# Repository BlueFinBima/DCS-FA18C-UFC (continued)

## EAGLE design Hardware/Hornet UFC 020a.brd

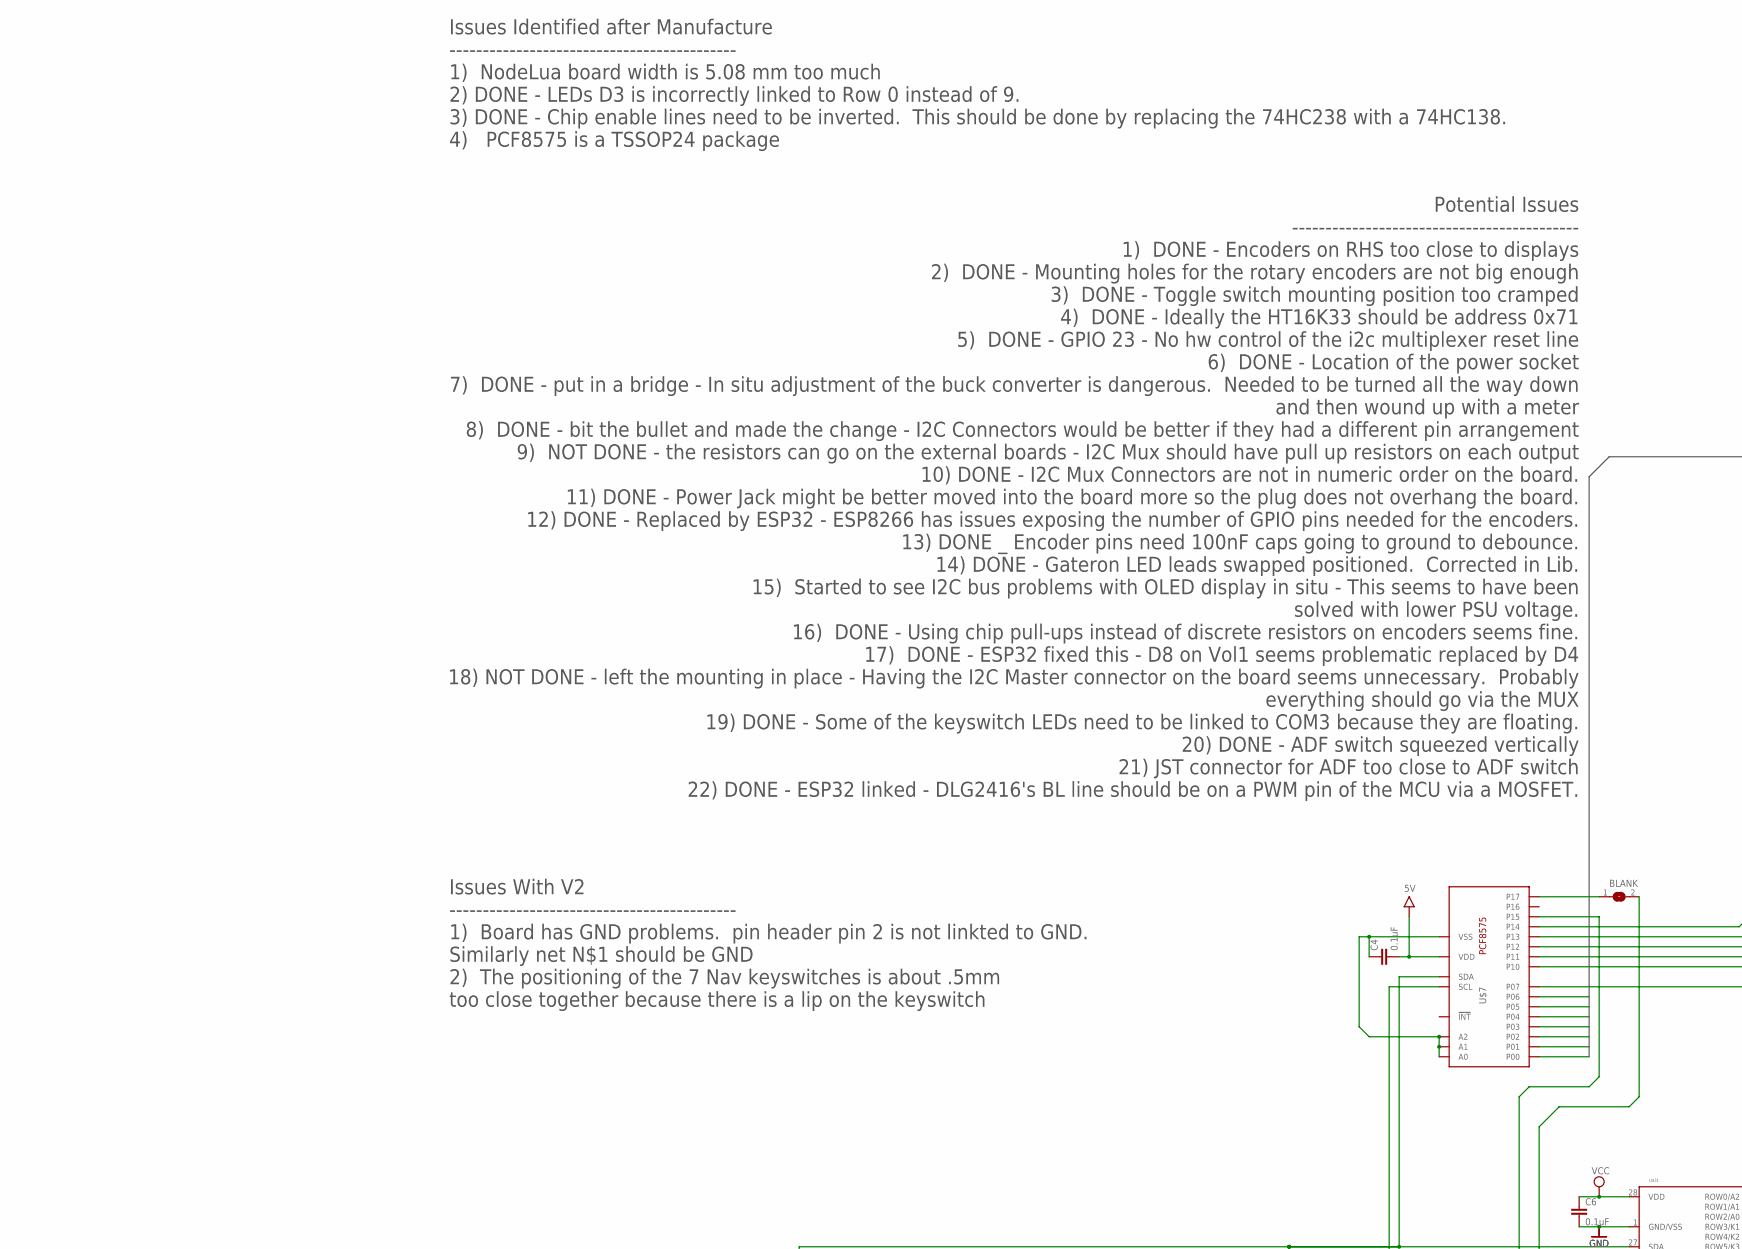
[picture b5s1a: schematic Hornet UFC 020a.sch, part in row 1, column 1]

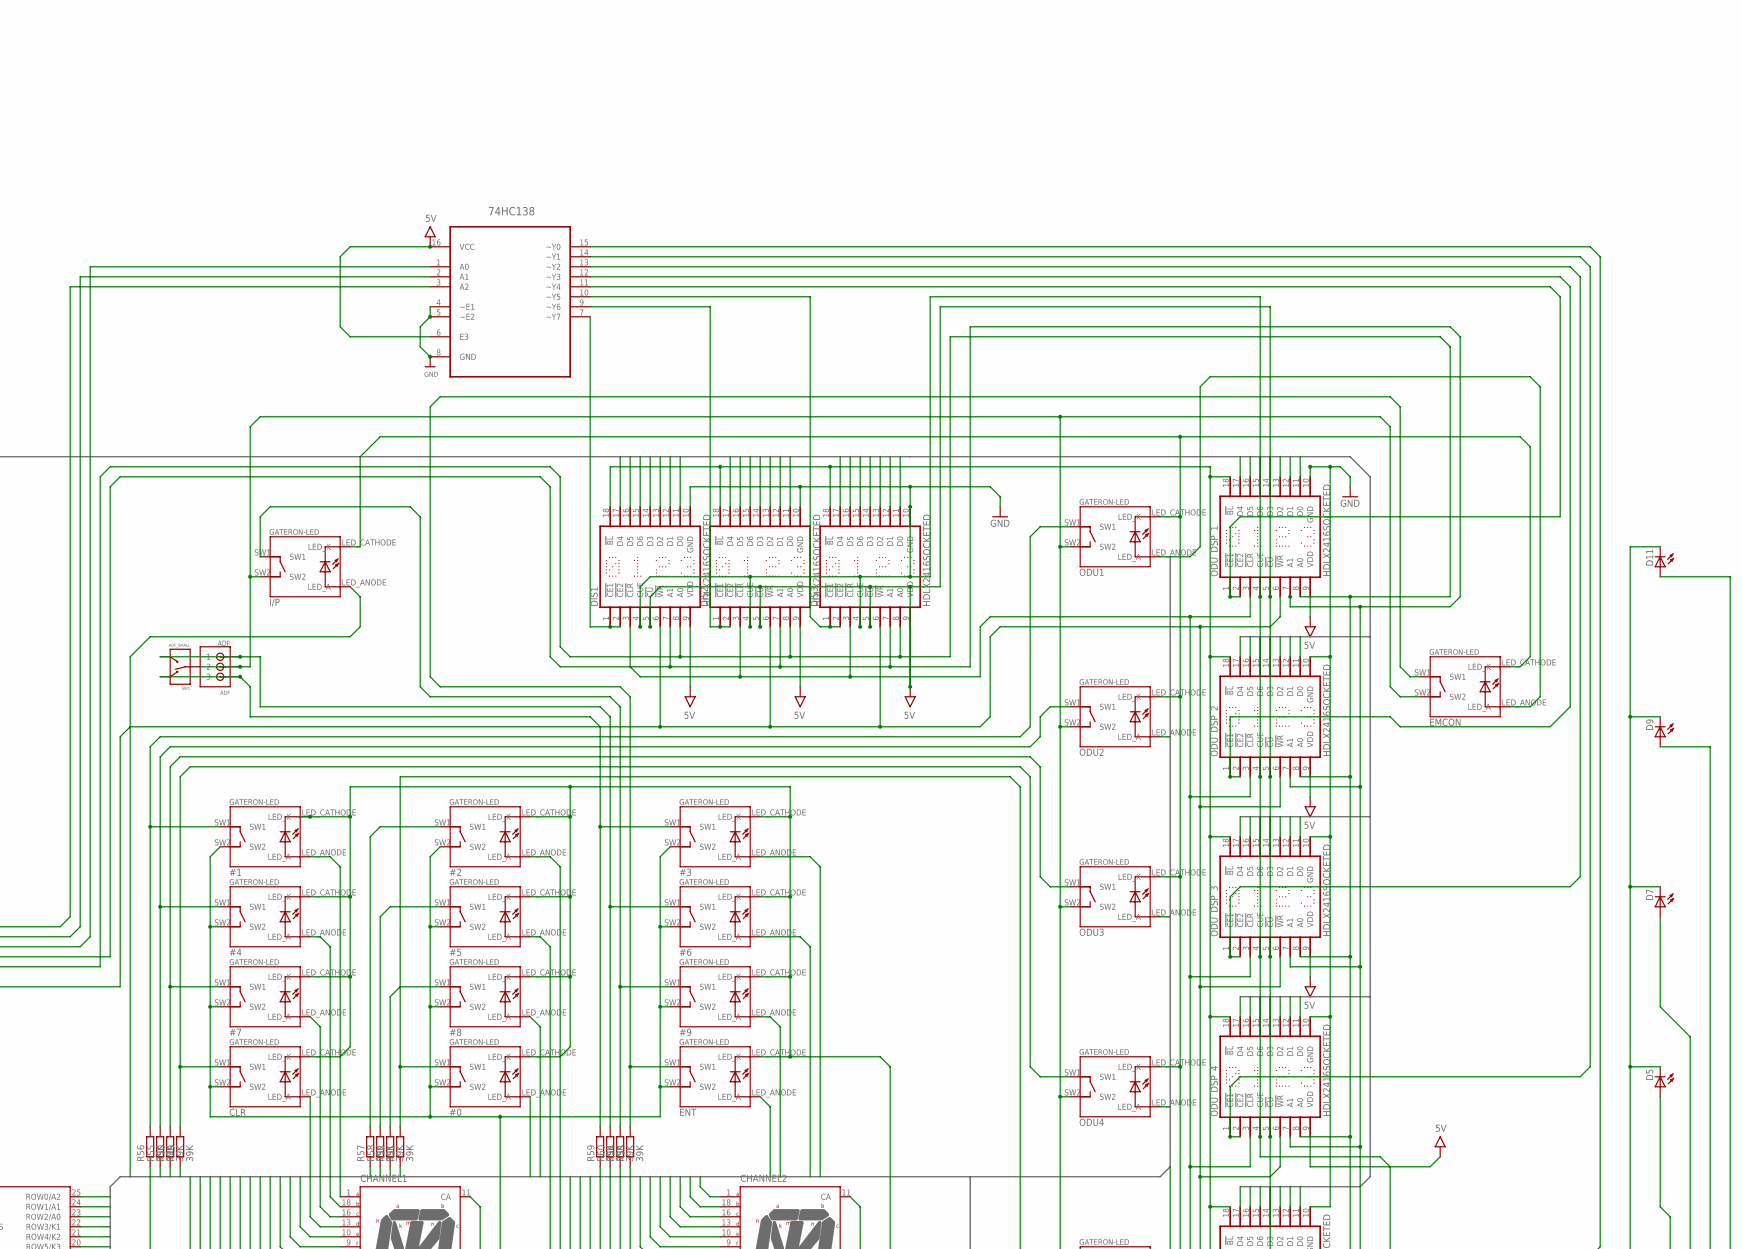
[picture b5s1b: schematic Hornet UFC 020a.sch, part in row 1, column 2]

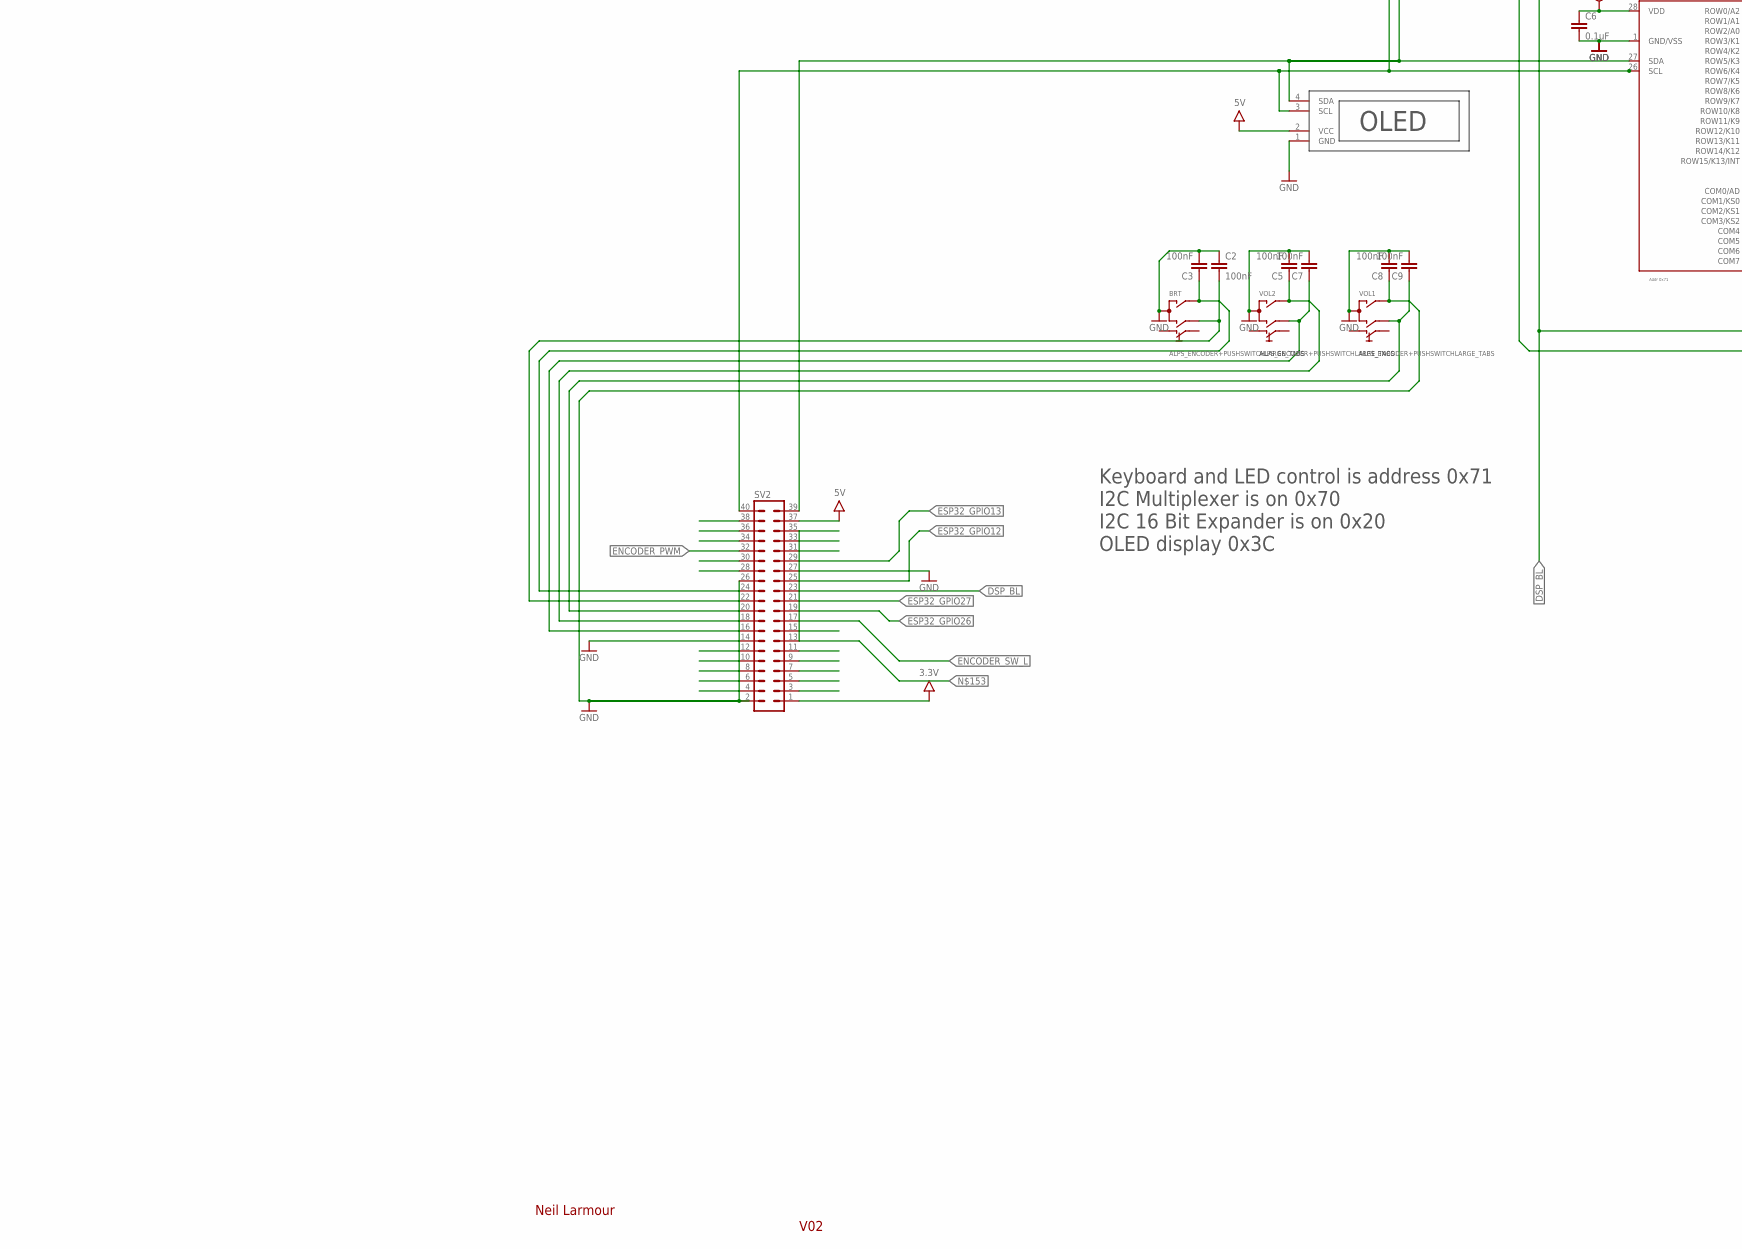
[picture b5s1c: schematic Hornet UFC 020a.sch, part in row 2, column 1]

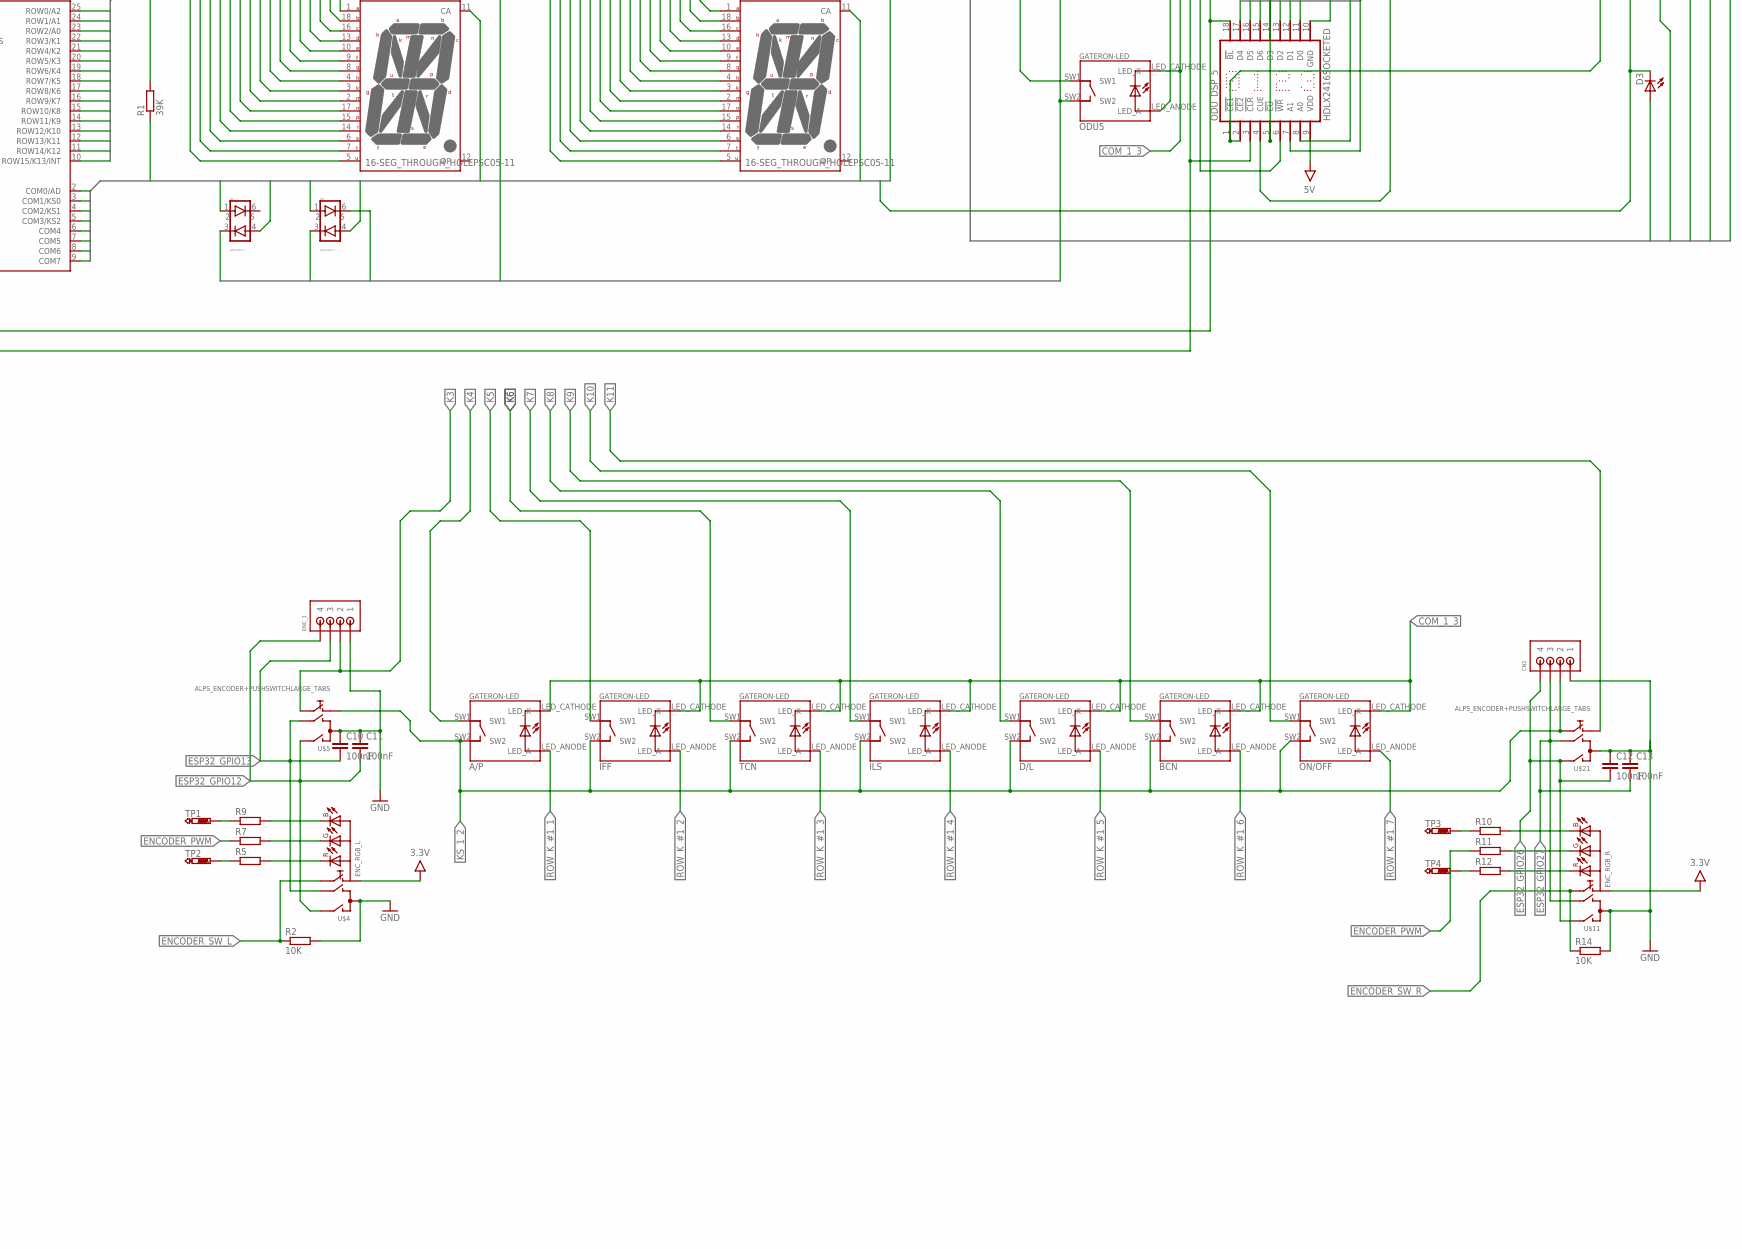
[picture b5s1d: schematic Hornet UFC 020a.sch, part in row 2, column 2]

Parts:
74HC138: CD74HC138M; SOIC127P600X175-16N
#0, #1, #2, #3, #4, #5, #6, #7, #8, #9: GATERON-LED
A/P: GATERON-LED
ADF: ADF; B3B-PH-SOLDER
BCN: GATERON-LED
BLANK: SOLDERJUMPERCLOSED; SOLDERJUMPER_CLOSEDWIRE
BRT: ALPS_ENCODER+PUSHSWITCHLARGE_TABS; ENCODER+SWITCH_LARGER_TABS
C2, C3, C5, C7, C8, C9, C10, C11, C12, C13: 100nF; C0805
C4, C6: 0.1uF; C0805
CHANNEL1, CHANNEL2: 16-SEG_THROUGH_HOLEPSC05-11; PSC05-11
CLR: GATERON-LED
CN2: JST-PH-B4B-PH-SM4THRU-HOLE; B4B-PH-SOLDER
D1, D2: BAT54CDW-7-F; SSOT6
D3, D5, D7, D9, D11: LED3MM_V_OFFSET; LED5X2MM_RECT_3MM_VOFFSET
D/L: GATERON-LED
DIS1, DIS2, DIS3: HDLX2416SOCKETED; HDLX2416(SOCKETED)
EMCON: GATERON-LED
ENC_1: JST-PH-B4B-PH-SM4THRU-HOLE; B4B-PH-SOLDER
ENT: GATERON-LED
I/P: GATERON-LED
IFF: GATERON-LED
ILS: GATERON-LED
ODU1, ODU2, ODU3, ODU4, ODU5: GATERON-LED
ODU_DSP_1, ODU_DSP_2, ODU_DSP_3, ODU_DSP_4, ODU_DSP_5: HDLX2416SOCKETED; HDLX2416(SOCKETED)
ON/OFF: GATERON-LED
R1, R49, R50, R51, R52, R53, R54, R55, R56, R57, R58, R59, R60: 39K; R1206
R2, R14: 10K; R0805
R5, R7, R9, R10, R11, R12: R-EU_R0805; R0805
SV2: MA20-2
SW1: ADF_SMALL; MICRO_TOGGLE_SPDT
TCN: GATERON-LED
TP1, TP2, TP3, TP4: PTR1TP13SQ; TP13SQ
U$4: ENC_RGB_L; ENCODER_RGB
U$5, U$21: ALPS_ENCODER+PUSHSWITCHLARGE_TABS; ENCODER+SWITCH_LARGER_TABS
U$7: PCF8575PWR; TSSOP24
U$11: ENC_RGB_R; ENCODER_RGB
U$31: Addr 0x71; SOIC28
U$37: OLED_128X32_I2C_DISPLAYTHROUGH_HOLE; OLED128X32_GRAPHICS_MODULE
VOL1, VOL2: ALPS_ENCODER+PUSHSWITCHLARGE_TABS; ENCODER+SWITCH_LARGER_TABS

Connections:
3.3V: U$4.ANODE (VCC), U$11.ANODE (VCC)
3V3: SV2.1
5V: 74HC138.6 (E3), 74HC138.16 (VCC), C4.2, C6.1, DIS1.5 (!CU), DIS1.9 (VDD), DIS2.5 (!CU), DIS2.9 (VDD), DIS3.5 (!CU), DIS3.9 (VDD), ODU_DSP_1.5 (!CU), ODU_DSP_1.9 (VDD), ODU_DSP_2.5 (!CU), ODU_DSP_2.9 (VDD), ODU_DSP_3.5 (!CU), ODU_DSP_3.9 (VDD), ODU_DSP_4.5 (!CU), ODU_DSP_4.9 (VDD), ODU_DSP_5.5 (!CU), ODU_DSP_5.9 (VDD), SV2.37, U$7.24 (VDD), U$31.28 (VDD), U$37.2 (VCC)
COM_1_0: CHANNEL1.11 (CA), D1.1 (A1), R1.1, U$31.2 (COM0/AD)
COM_1_1: CHANNEL2.11 (CA), D1.4 (A2), U$31.3 (COM1/KS0)
COM_1_2: #0.LED_CATHODE (LED_K), #1.LED_CATHODE (LED_K), #2.LED_CATHODE (LED_K), #3.LED_CATHODE (LED_K), #4.LED_CATHODE (LED_K), #5.LED_CATHODE (LED_K), #6.LED_CATHODE (LED_K), #7.LED_CATHODE (LED_K), #8.LED_CATHODE (LED_K), #9.LED_CATHODE (LED_K), CLR.LED_CATHODE (LED_K), D2.1 (A1), ENT.LED_CATHODE (LED_K), U$31.4 (COM2/KS1)
COM_1_3: A/P.LED_CATHODE (LED_K), BCN.LED_CATHODE (LED_K), D2.4 (A2), D/L.LED_CATHODE (LED_K), EMCON.LED_CATHODE (LED_K), I/P.LED_CATHODE (LED_K), IFF.LED_CATHODE (LED_K), ILS.LED_CATHODE (LED_K), ODU1.LED_CATHODE (LED_K), ODU2.LED_CATHODE (LED_K), ODU3.LED_CATHODE (LED_K), ODU4.LED_CATHODE (LED_K), ODU5.LED_CATHODE (LED_K), ON/OFF.LED_CATHODE (LED_K), TCN.LED_CATHODE (LED_K), U$31.5 (COM3/KS2)
COM_1_4: D3.K (C), D5.K (C), D7.K (C), D9.K (C), D11.K (C), U$31.6 (COM4)
COM_1_5: U$31.7 (COM5)
COM_1_6: U$31.8 (COM6)
COM_1_7: U$31.9 (COM7)
D0: DIS1.11 (D0), DIS2.11 (D0), DIS3.11 (D0), ODU_DSP_1.11 (D0), ODU_DSP_2.11 (D0), ODU_DSP_3.11 (D0), ODU_DSP_4.11 (D0), ODU_DSP_5.11 (D0), U$7.4 (P00)
D1: DIS1.12 (D1), DIS2.12 (D1), DIS3.12 (D1), ODU_DSP_1.12 (D1), ODU_DSP_2.12 (D1), ODU_DSP_3.12 (D1), ODU_DSP_4.12 (D1), ODU_DSP_5.12 (D1), U$7.5 (P01)
D2: DIS1.13 (D2), DIS2.13 (D2), DIS3.13 (D2), ODU_DSP_1.13 (D2), ODU_DSP_2.13 (D2), ODU_DSP_3.13 (D2), ODU_DSP_4.13 (D2), ODU_DSP_5.13 (D2), U$7.6 (P02)
D3: DIS1.14 (D3), DIS2.14 (D3), DIS3.14 (D3), ODU_DSP_1.14 (D3), ODU_DSP_2.14 (D3), ODU_DSP_3.14 (D3), ODU_DSP_4.14 (D3), ODU_DSP_5.14 (D3), U$7.7 (P03)
D4: DIS1.17 (D4), DIS2.17 (D4), DIS3.17 (D4), ODU_DSP_1.17 (D4), ODU_DSP_2.17 (D4), ODU_DSP_3.17 (D4), ODU_DSP_4.17 (D4), ODU_DSP_5.17 (D4), U$7.8 (P04)
D5: DIS1.16 (D5), DIS2.16 (D5), DIS3.16 (D5), ODU_DSP_1.16 (D5), ODU_DSP_2.16 (D5), ODU_DSP_3.16 (D5), ODU_DSP_4.16 (D5), ODU_DSP_5.16 (D5), U$7.9 (P05)
D6: DIS1.15 (D6), DIS2.15 (D6), DIS3.15 (D6), ODU_DSP_1.15 (D6), ODU_DSP_2.15 (D6), ODU_DSP_3.15 (D6), ODU_DSP_4.15 (D6), ODU_DSP_5.15 (D6), U$7.10 (P06)
DSP3: BRT.B, C2.2, SV2.22
DSP_A0: DIS1.8 (A0), DIS2.8 (A0), DIS3.8 (A0), ODU_DSP_1.8 (A0), ODU_DSP_2.8 (A0), ODU_DSP_3.8 (A0), ODU_DSP_4.8 (A0), ODU_DSP_5.8 (A0), U$7.13 (P10)
DSP_A1: DIS1.7 (A1), DIS2.7 (A1), DIS3.7 (A1), ODU_DSP_1.7 (A1), ODU_DSP_2.7 (A1), ODU_DSP_3.7 (A1), ODU_DSP_4.7 (A1), ODU_DSP_5.7 (A1), U$7.14 (P11)
DSP_BL: BLANK.2, DIS1.18 (!BL), DIS2.18 (!BL), DIS3.18 (!BL), ODU_DSP_1.18 (!BL), ODU_DSP_2.18 (!BL), ODU_DSP_3.18 (!BL), ODU_DSP_4.18 (!BL), ODU_DSP_5.18 (!BL), SV2.23
DSP_CLR: DIS1.3 (!CLR), DIS2.3 (!CLR), DIS3.3 (!CLR), ODU_DSP_1.3 (!CLR), ODU_DSP_2.3 (!CLR), ODU_DSP_3.3 (!CLR), ODU_DSP_4.3 (!CLR), ODU_DSP_5.3 (!CLR), U$7.18 (P15)
ENCODER_PWM: R7.1, R11.1, SV2.32
ENCODER_SW_L: R2.1, SV2.17, U$4.SWITCH (E)
ENCODER_SW_R: R14.1, U$11.SWITCH (E)
ESP32_GPIO12: C11.2, ENC_1.P4 (4), SV2.25, U$4.A, U$5.A
ESP32_GPIO13: C10.2, ENC_1.P3 (3), SV2.29, U$4.B, U$5.B
ESP32_GPIO26: C12.2, CN2.P4 (4), SV2.19, U$11.A, U$21.A
ESP32_GPIO27: C13.2, CN2.P3 (3), SV2.21, U$11.B, U$21.B
GND: 74HC138.4 (~E1), 74HC138.5 (~E2), 74HC138.8 (GND), BRT.C, C2.1, C3.2, C5.2, C6.2, C7.2, C8.1, C8.2, C9.2, C10.1, C11.1, C12.1, C13.1, CN2.P1 (1), DIS1.4 (CUE), DIS1.10 (GND), DIS2.4 (CUE), DIS2.10 (GND), DIS3.4 (CUE), DIS3.10 (GND), ENC_1.P1 (1), ODU_DSP_1.4 (CUE), ODU_DSP_1.10 (GND), ODU_DSP_2.4 (CUE), ODU_DSP_2.10 (GND), ODU_DSP_3.4 (CUE), ODU_DSP_3.10 (GND), ODU_DSP_4.4 (CUE), ODU_DSP_4.10 (GND), ODU_DSP_5.4 (CUE), ODU_DSP_5.10 (GND), R2.2, R14.2, SV2.2, SV2.14, SV2.26, SV2.27, U$4.C, U$5.C, U$11.C, U$21.C, U$31.1 (GND/VSS), U$37.1 (GND), VOL1.A, VOL1.C, VOL2.C
I2C_0: SV2.39, U$7.23 (SDA), U$31.27 (SDA), U$37.4 (SDA)
I2C_1: SV2.40, U$7.22 (SCL), U$31.26 (SCL), U$37.3 (SCL)
K3: #1.SW1, ENC_1.P2 (2), ODU1.SW1, R56.2, U$5.E
K4: #2.SW1, A/P.SW1, R57.2
K5: #3.SW1, ADF.P3 (3), IFF.SW1, R59.2, SW1.A$1
K6: #4.SW1, ODU2.SW1, R55.2, TCN.SW1
K7: #5.SW1, ILS.SW1, R58.2
K8: #6.SW1, ADF.P1 (1), D/L.SW1, R60.2, SW1.B$1
K9: #7.SW1, BCN.SW1, ODU3.SW1, R50.2
K10: #8.SW1, ON/OFF.SW1, R52.2
K11: #9.SW1, I/P.SW1, R54.2, U$21.D
K12: CLR.SW1, ODU4.SW1, R49.2
K13: #0.SW1, ODU5.SW1, R51.2
K14: EMCON.SW1, ENT.SW1, R53.2
KS_1_0: #0.SW2, #1.SW2, #2.SW2, #3.SW2, #4.SW2, #5.SW2, #6.SW2, #7.SW2, #8.SW2, #9.SW2, CLR.SW2, D1.3 (C2), ENT.SW2
KS_1_1: ADF.P2 (2), D2.6 (C1), EMCON.SW2, I/P.SW2, ODU1.SW2, ODU2.SW2, ODU3.SW2, ODU4.SW2, ODU5.SW2, SW1.C$1
KS_1_2: A/P.SW2, BCN.SW2, CN2.P2 (2), D2.3 (C2), D/L.SW2, IFF.SW2, ILS.SW2, ON/OFF.SW2, TCN.SW2, U$5.D, U$21.E
unnamed: C4.1, U$7.2 (A1), U$7.3 (A2), U$7.12 (VSS), U$7.21 (A0)
unnamed: R9.2, U$4.BLUE (LED_B)
unnamed: 74HC138.1 (A0), U$7.15 (P12)
unnamed: 74HC138.2 (A1), U$7.16 (P13)
unnamed: BLANK.1, U$7.20 (P17)
unnamed: 74HC138.3 (A2), U$7.17 (P14)
unnamed: 74HC138.10 (~Y5), DIS3.1 (!CE1), DIS3.2 (!CE2)
unnamed: C9.1, SV2.20, VOL1.B
unnamed: 74HC138.7 (~Y7), DIS1.1 (!CE1), DIS1.2 (!CE2)
unnamed: 74HC138.9 (~Y6), DIS2.1 (!CE1), DIS2.2 (!CE2)
unnamed: 74HC138.11 (~Y4), ODU_DSP_1.1 (!CE1), ODU_DSP_1.2 (!CE2)
unnamed: 74HC138.12 (~Y3), ODU_DSP_2.1 (!CE1), ODU_DSP_2.2 (!CE2)
unnamed: 74HC138.13 (~Y2), ODU_DSP_3.1 (!CE1), ODU_DSP_3.2 (!CE2)
unnamed: 74HC138.14 (~Y1), ODU_DSP_4.1 (!CE1), ODU_DSP_4.2 (!CE2)
unnamed: 74HC138.15 (~Y0), ODU_DSP_5.1 (!CE1), ODU_DSP_5.2 (!CE2)
unnamed: DIS1.6 (!WR), DIS2.6 (!WR), DIS3.6 (!WR), ODU_DSP_1.6 (!WR), ODU_DSP_2.6 (!WR), ODU_DSP_3.6 (!WR), ODU_DSP_4.6 (!WR), ODU_DSP_5.6 (!WR), U$7.11 (P07)
unnamed: BRT.A, C3.1, SV2.24
unnamed: R7.2, U$4.GREEN (LED_G)
unnamed: R12.2, U$11.RED (LED_R)
unnamed: R11.2, U$11.GREEN (LED_G)
unnamed: R10.2, U$11.BLUE (LED_B)
unnamed: R5.2, U$4.RED (LED_R)
unnamed: R12.1, TP4.TP
unnamed: R5.1, TP2.TP
unnamed: R9.1, TP1.TP
unnamed: R10.1, TP3.TP
unnamed: C5.1, SV2.18, VOL2.A
unnamed: C7.1, SV2.16, VOL2.B
unnamed: SV2.13, SV2.35
ROW_K_#1_0: #1.LED_ANODE (LED_A), CHANNEL1.1 (A), CHANNEL2.1 (A), ODU1.LED_ANODE (LED_A), U$31.25 (ROW0/A2)
ROW_K_#1_1: #2.LED_ANODE (LED_A), A/P.LED_ANODE (LED_A), CHANNEL1.18 (B), CHANNEL2.18 (B), D11.A, ODU2.LED_ANODE (LED_A), U$31.24 (ROW1/A1)
ROW_K_#1_2: #3.LED_ANODE (LED_A), CHANNEL1.16 (C), CHANNEL2.16 (C), IFF.LED_ANODE (LED_A), ODU3.LED_ANODE (LED_A), R1.2, U$31.23 (ROW2/A0)
ROW_K_#1_3: #4.LED_ANODE (LED_A), CHANNEL1.13 (D), CHANNEL2.13 (D), D9.A, ODU4.LED_ANODE (LED_A), R56.1, TCN.LED_ANODE (LED_A), U$31.22 (ROW3/K1)
ROW_K_#1_4: #5.LED_ANODE (LED_A), CHANNEL1.10 (E), CHANNEL2.10 (E), ILS.LED_ANODE (LED_A), ODU5.LED_ANODE (LED_A), R57.1, U$31.21 (ROW4/K2)
ROW_K_#1_5: #6.LED_ANODE (LED_A), CHANNEL1.9 (F), CHANNEL2.9 (F), D7.A, D/L.LED_ANODE (LED_A), EMCON.LED_ANODE (LED_A), R59.1, U$31.20 (ROW5/K3)
ROW_K_#1_6: #7.LED_ANODE (LED_A), BCN.LED_ANODE (LED_A), CHANNEL1.8 (G), CHANNEL2.8 (G), I/P.LED_ANODE (LED_A), R55.1, U$31.19 (ROW6/K4)
ROW_K_#1_7: #8.LED_ANODE (LED_A), CHANNEL1.4 (H), CHANNEL2.4 (H), D5.A, ON/OFF.LED_ANODE (LED_A), R58.1, U$31.18 (ROW7/K5)
ROW_K_#1_8: #9.LED_ANODE (LED_A), CHANNEL1.3 (K), CHANNEL2.3 (K), R60.1, U$31.17 (ROW8/K6)
ROW_K_#1_9: CHANNEL1.2 (M), CHANNEL2.2 (M), CLR.LED_ANODE (LED_A), D3.A, R50.1, U$31.16 (ROW9/K7)
ROW_K_#1_10: #0.LED_ANODE (LED_A), CHANNEL1.17 (N), CHANNEL2.17 (N), R52.1, U$31.15 (ROW10/K8)
ROW_K_#1_11: CHANNEL1.15, CHANNEL2.15, ENT.LED_ANODE (LED_A), R54.1, U$31.14 (ROW11/K9)
ROW_K_#1_12: CHANNEL1.14 (R), CHANNEL2.14 (R), R49.1, U$31.13 (ROW12/K10)
ROW_K_#1_13: CHANNEL1.6 (S), CHANNEL2.6 (S), R51.1, U$31.12 (ROW13/K11)
ROW_K_#1_14: CHANNEL1.7 (T), CHANNEL2.7 (T), R53.1, U$31.11 (ROW14/K12)
ROW_K_#1_15: CHANNEL1.5 (U), CHANNEL2.5 (U), U$31.10 (ROW15/K13/INT)
SCL3V3: SV2.6
SDA3V1: SV2.4
SDA3V3: SV2.12

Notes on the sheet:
V02
Neil Larmour
Keyboard and LED control is address 0x71 I2C Multiplexer is on 0x70 I2C 16 Bit Expander is on 0x20 OLED display 0x3C
Issues Identified after Manufacture ------------------------------------------- 1) NodeLua board width is 5.08 mm too much 2) DONE - LEDs D3 is incorrectly linked to Row 0 instead of 9. 3) DONE - Chip enable lines need to be inverted. This should be done by replacing the 74HC238 with a 74HC138. 4) 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
Potential Issues ------------------------------------------- 1) DONE - Encoders on RHS too close to displays 2) DONE - Mounting holes for the rotary encoders are not big enough 3) DONE - Toggle switch mounting position too cramped 4) DONE - Ideally the HT16K33 should be address 0x71 5) DONE - GPIO 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
Issues With V2 ------------------------------------------- 1) Board has GND problems. pin header pin 2 is not linkted to GND. Similarly net N$1 should be GND 2) The positioning of the 7 Nav keyswitches is about .5mm too close together because there is a lip on the keyswitch

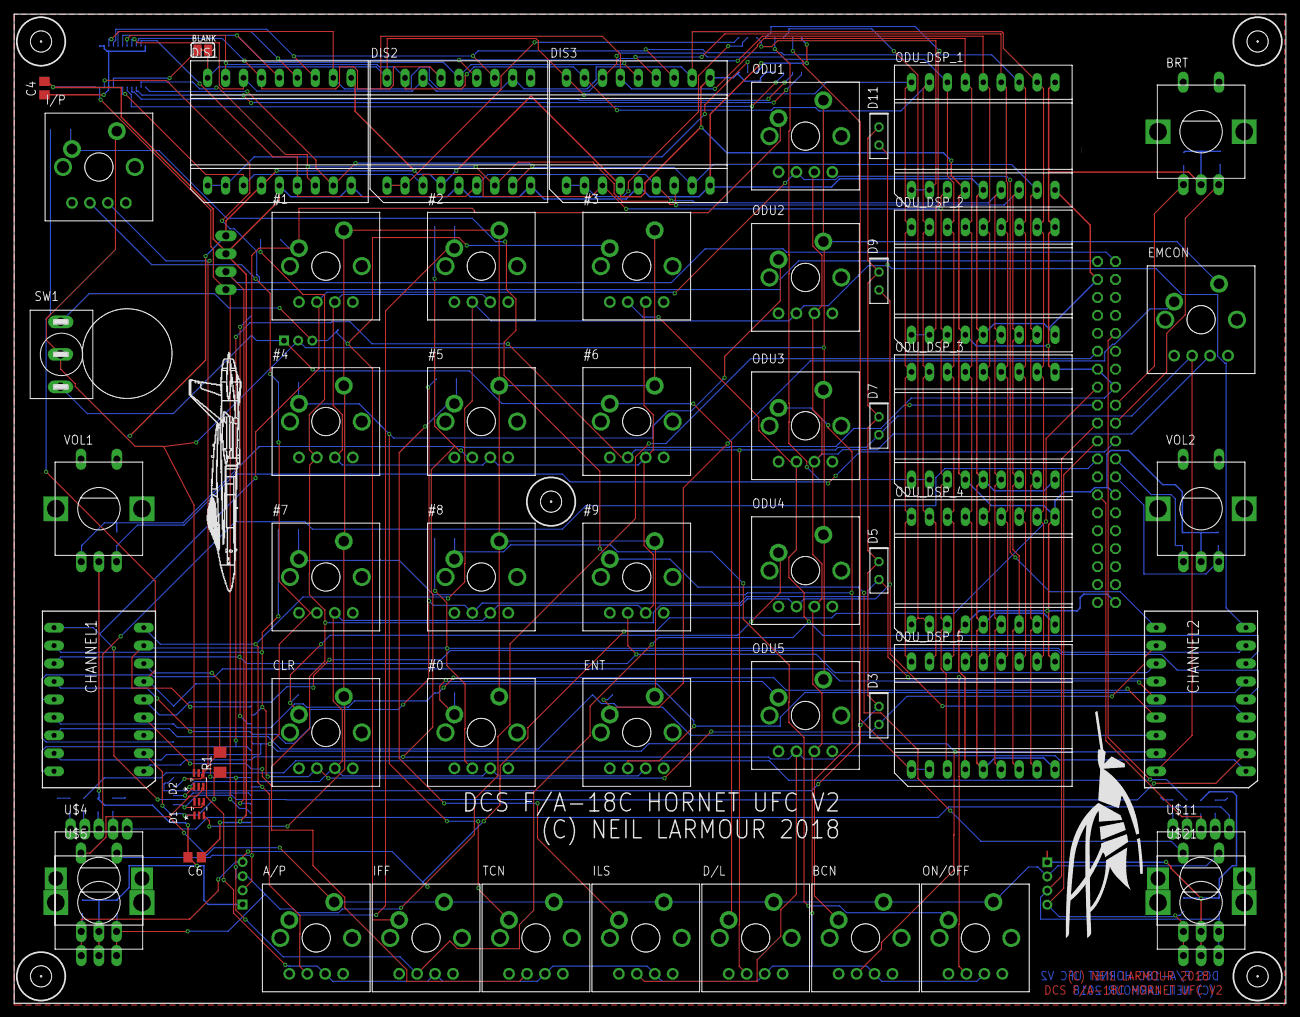
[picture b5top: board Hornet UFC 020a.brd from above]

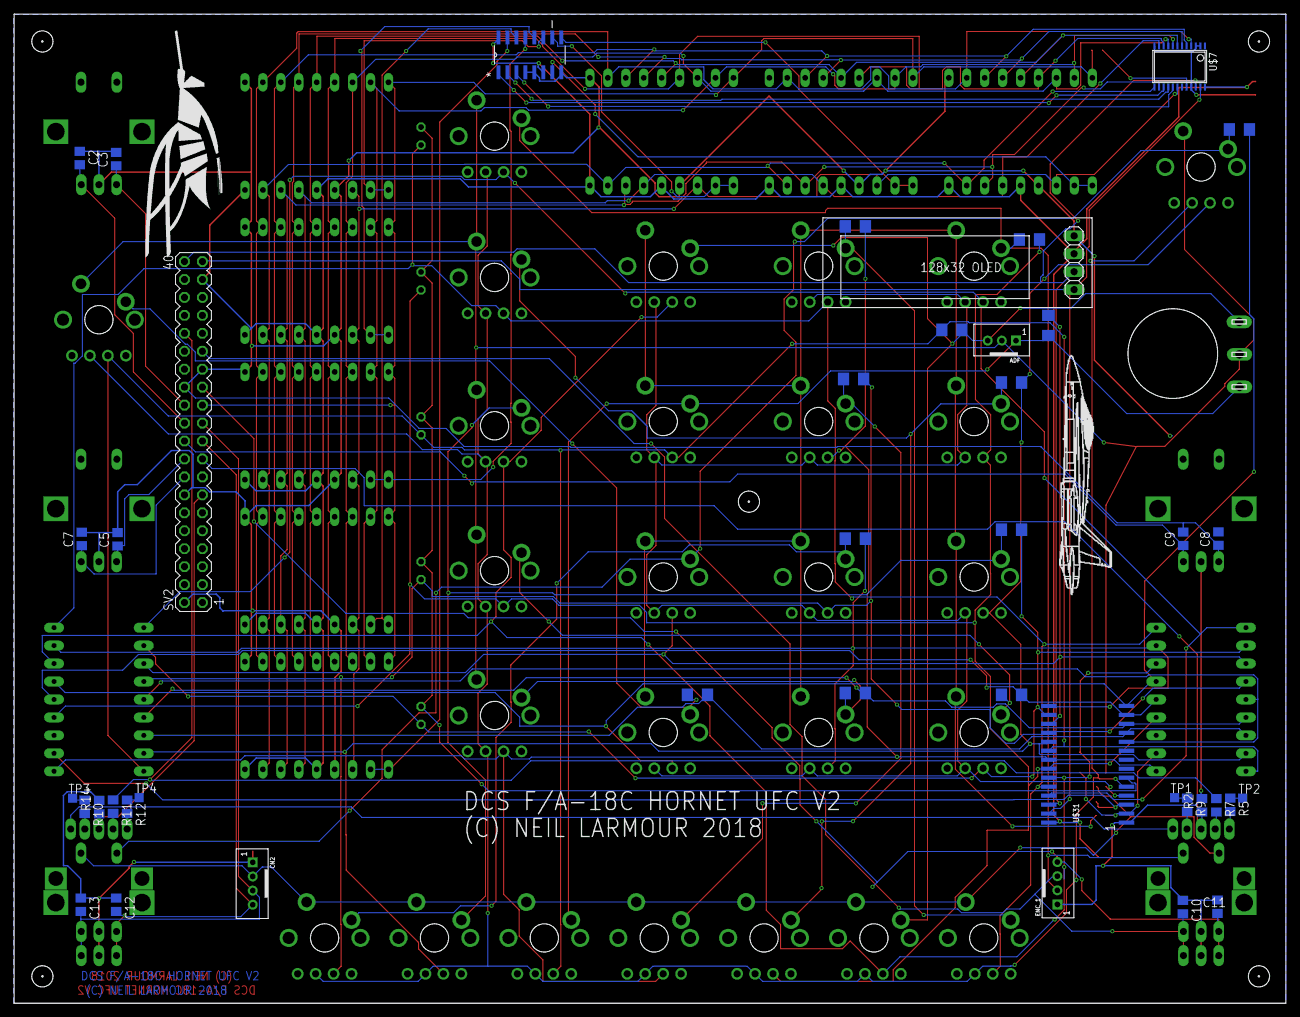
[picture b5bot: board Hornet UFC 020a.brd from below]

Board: 2 copper layers, 180.0 x 140.0 mm, 102 parts (42 on the bottom side), 89 nets.

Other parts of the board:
U$3, U$25, U$26, U$34, U$39: DRIL-3

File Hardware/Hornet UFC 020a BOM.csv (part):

"Part;""Value"";""Device"";""Package"";""Description"";""MF"";""MPN"";""OC_FARNELL"";""OC_NEWARK"";""PACKAGE"";""SPICEPREFIX"";""SUPPLIER"";""TP_SIGNAL_NAME"";",
"#0;""GATERON-LED"";""GATERON-LED"";""GATERON-LED"";""Gateron keyswitch with LED"";"""";"""";"""";"""";"""";"""";"""";"""";",
"#1;""GATERON-LED"";""GATERON-LED"";""GATERON-LED"";""Gateron keyswitch with LED"";"""";"""";"""";"""";"""";"""";"""";"""";",
"#2;""GATERON-LED"";""GATERON-LED"";""GATERON-LED"";""Gateron keyswitch with LED"";"""";"""";"""";"""";"""";"""";"""";"""";",
"#3;""GATERON-LED"";""GATERON-LED"";""GATERON-LED"";""Gateron keyswitch with LED"";"""";"""";"""";"""";"""";"""";"""";"""";",
"#4;""GATERON-LED"";""GATERON-LED"";""GATERON-LED"";""Gateron keyswitch with LED"";"""";"""";"""";"""";"""";"""";"""";"""";",
"#5;""GATERON-LED"";""GATERON-LED"";""GATERON-LED"";""Gateron keyswitch with LED"";"""";"""";"""";"""";"""";"""";"""";"""";",
"#6;""GATERON-LED"";""GATERON-LED"";""GATERON-LED"";""Gateron keyswitch with LED"";"""";"""";"""";"""";"""";"""";"""";"""";",
"#7;""GATERON-LED"";""GATERON-LED"";""GATERON-LED"";""Gateron keyswitch with LED"";"""";"""";"""";"""";"""";"""";"""";"""";",
"#8;""GATERON-LED"";""GATERON-LED"";""GATERON-LED"";""Gateron keyswitch with LED"";"""";"""";"""";"""";"""";"""";"""";"""";",
"#9;""GATERON-LED"";""GATERON-LED"";""GATERON-LED"";""Gateron keyswitch with LED"";"""";"""";"""";"""";"""";"""";"""";"""";",
"74HC138;""CD74HC138M"";""CD74HC138M"";""SOIC127P600X175-16N"";""High-Speed CMOS Logic 3- to 8-Line Decoder/Demultiplexer Inverting and Noninverting"";"""";""CD74HC138M"";""1640756"";""66F5206"";""SOIC-16"";"""";""Texas Instruments"";"""";",
"A/P;""GATERON-LED"";""GATERON-LED"";""GATERON-LED"";""Gateron keyswitch with LED"";"""";"""";"""";"""";"""";"""";"""";"""";",
"ADF;""ADF"";""JST-PH-B2B-SM3SOLDER"";""B3B-PH-SOLDER"";""JST PH Connector 2mm Pitch (3 Pin)"";"""";"""";"""";"""";"""";"""";"""";"""";",
"BCN;""GATERON-LED"";""GATERON-LED"";""GATERON-LED"";""Gateron keyswitch with LED"";"""";"""";"""";"""";"""";"""";"""";"""";",
"BLANK;"""";""SOLDERJUMPERCLOSED"";""SOLDERJUMPER_CLOSEDWIRE"";""SMD Solder JUMPER"";"""";"""";"""";"""";"""";"""";"""";"""";",
"BRT;""ALPS_ENCODER+PUSHSWITCHLARGE_TABS"";""ALPS_ENCODER+PUSHSWITCHLARGE_TABS"";""ENCODER+SWITCH_LARGER_TABS"";"""";"""";"""";"""";"""";"""";"""";"""";"""";",
"C2;""100nF"";""C-EUC0805"";""C0805"";""CAPACITOR"," European symbol"";"""";"""";"""";"""";"""";"""";"""";"""";"
"C3;""100nF"";""C-EUC0805"";""C0805"";""CAPACITOR"," European symbol"";"""";"""";"""";"""";"""";"""";"""";"""";"
"C4;""0.1uF"";""C-EUC0805"";""C0805"";""CAPACITOR"," European symbol"";"""";"""";"""";"""";"""";"""";"""";"""";"
"C5;""100nF"";""C-EUC0805"";""C0805"";""CAPACITOR"," European symbol"";"""";"""";"""";"""";"""";"""";"""";"""";"
"C6;""0.1uF"";""C-EUC0805"";""C0805"";""CAPACITOR"," European symbol"";"""";"""";"""";"""";"""";"""";"""";"""";"
"C7;""100nF"";""C-EUC0805"";""C0805"";""CAPACITOR"," European symbol"";"""";"""";"""";"""";"""";"""";"""";"""";"
"C8;""100nF"";""C-EUC0805"";""C0805"";""CAPACITOR"," European symbol"";"""";"""";"""";"""";"""";"""";"""";"""";"
"C9;""100nF"";""C-EUC0805"";""C0805"";""CAPACITOR"," European symbol"";"""";"""";"""";"""";"""";"""";"""";"""";"
"C10;""100nF"";""C-EUC0805"";""C0805"";""CAPACITOR"," European symbol"";"""";"""";"""";"""";"""";"""";"""";"""";"
"C11;""100nF"";""C-EUC0805"";""C0805"";""CAPACITOR"," European symbol"";"""";"""";"""";"""";"""";"""";"""";"""";"
"C12;""100nF"";""C-EUC0805"";""C0805"";""CAPACITOR"," European symbol"";"""";"""";"""";"""";"""";"""";"""";"""";"
"C13;""100nF"";""C-EUC0805"";""C0805"";""CAPACITOR"," European symbol"";"""";"""";"""";"""";"""";"""";"""";"""";"
"CHANNEL1;""16-SEG_THROUGH_HOLEPSC05-11"";""16-SEG_THROUGH_HOLEPSC05-11"";""PSC05-11"";""16 SEGMENT SINGLE DIGIT ALPHANUMERIC NUMERIC DISPLAY"";"""";"""";"""";"""";"""";"""";"""";"""";",
"CHANNEL2;""16-SEG_THROUGH_HOLEPSC05-11"";""16-SEG_THROUGH_HOLEPSC05-11"";""PSC05-11"";""16 SEGMENT SINGLE DIGIT ALPHANUMERIC NUMERIC DISPLAY"";"""";"""";"""";"""";"""";"""";"""";"""";",
"CLR;""GATERON-LED"";""GATERON-LED"";""GATERON-LED"";""Gateron keyswitch with LED"";"""";"""";"""";"""";"""";"""";"""";"""";",
"CN2;""JST-PH-B4B-PH-SM4THRU-HOLE"";""JST-PH-B4B-PH-SM4THRU-HOLE"";""B4B-PH-SOLDER"";""JST PH 4 Pin (2.00"")"";"""";"""";"""";"""";"""";"""";"""";"""";",
"D/L;""GATERON-LED"";""GATERON-LED"";""GATERON-LED"";""Gateron keyswitch with LED"";"""";"""";"""";"""";"""";"""";"""";"""";",
"D1;""BAT54CDW"";""BAT54CDW"";""SSOT6"";"""";"""";"""";"""";"""";"""";"""";"""";"""";",
"D2;""BAT54CDW"";""BAT54CDW"";""SSOT6"";"""";"""";"""";"""";"""";"""";"""";"""";"""";",
"D3;"""";""LED3MM_V_OFFSET"";""LED5X2MM_RECT_3MM_VOFFSET"";""LED"";"""";"""";"""";"""";"""";"""";"""";"""";",
"D5;"""";""LED3MM_V_OFFSET"";""LED5X2MM_RECT_3MM_VOFFSET"";""LED"";"""";"""";"""";"""";"""";"""";"""";"""";",
"D7;"""";""LED3MM_V_OFFSET"";""LED5X2MM_RECT_3MM_VOFFSET"";""LED"";"""";"""";"""";"""";"""";"""";"""";"""";",
"D9;"""";""LED3MM_V_OFFSET"";""LED5X2MM_RECT_3MM_VOFFSET"";""LED"";"""";"""";"""";"""";"""";"""";"""";"""";",
"D11;"""";""LED3MM_V_OFFSET"";""LED5X2MM_RECT_3MM_VOFFSET"";""LED"";"""";"""";"""";"""";"""";"""";"""";"""";",
"DIS1;""HDLX2416SOCKETED"";""HDLX2416SOCKETED"";""HDLX2416(SOCKETED)"";""LED DISPLAY"";"""";"""";"""";"""";"""";"""";"""";"""";",
"DIS2;""HDLX2416SOCKETED"";""HDLX2416SOCKETED"";""HDLX2416(SOCKETED)"";""LED DISPLAY"";"""";"""";"""";"""";"""";"""";"""";"""";",
"DIS3;""HDLX2416SOCKETED"";""HDLX2416SOCKETED"";""HDLX2416(SOCKETED)"";""LED DISPLAY"";"""";"""";"""";"""";"""";"""";"""";"""";",
"EMCON;""GATERON-LED"";""GATERON-LED"";""GATERON-LED"";""Gateron keyswitch with LED"";"""";"""";"""";"""";"""";"""";"""";"""";",
"ENC_1;""JST-PH-B4B-PH-SM4THRU-HOLE"";""JST-PH-B4B-PH-SM4THRU-HOLE"";""B4B-PH-SOLDER"";""JST PH 4 Pin (2.00"")"";"""";"""";"""";"""";"""";"""";"""";"""";",
"ENT;""GATERON-LED"";""GATERON-LED"";""GATERON-LED"";""Gateron keyswitch with LED"";"""";"""";"""";"""";"""";"""";"""";"""";",
"I/P;""GATERON-LED"";""GATERON-LED"";""GATERON-LED"";""Gateron keyswitch with LED"";"""";"""";"""";"""";"""";"""";"""";"""";",
"IFF;""GATERON-LED"";""GATERON-LED"";""GATERON-LED"";""Gateron keyswitch with LED"";"""";"""";"""";"""";"""";"""";"""";"""";",
"ILS;""GATERON-LED"";""GATERON-LED"";""GATERON-LED"";""Gateron keyswitch with LED"";"""";"""";"""";"""";"""";"""";"""";"""";",
"ODU1;""GATERON-LED"";""GATERON-LED"";""GATERON-LED"";""Gateron keyswitch with LED"";"""";"""";"""";"""";"""";"""";"""";"""";",
"ODU2;""GATERON-LED"";""GATERON-LED"";""GATERON-LED"";""Gateron keyswitch with LED"";"""";"""";"""";"""";"""";"""";"""";"""";",
"ODU3;""GATERON-LED"";""GATERON-LED"";""GATERON-LED"";""Gateron keyswitch with LED"";"""";"""";"""";"""";"""";"""";"""";"""";",
"ODU4;""GATERON-LED"";""GATERON-LED"";""GATERON-LED"";""Gateron keyswitch with LED"";"""";"""";"""";"""";"""";"""";"""";"""";",
"ODU5;""GATERON-LED"";""GATERON-LED"";""GATERON-LED"";""Gateron keyswitch with LED"";"""";"""";"""";"""";"""";"""";"""";"""";",
"ODU_DSP_1;""HDLX2416SOCKETED"";""HDLX2416SOCKETED"";""HDLX2416(SOCKETED)"";""LED DISPLAY"";"""";"""";"""";"""";"""";"""";"""";"""";",
"ODU_DSP_2;""HDLX2416SOCKETED"";""HDLX2416SOCKETED"";""HDLX2416(SOCKETED)"";""LED DISPLAY"";"""";"""";"""";"""";"""";"""";"""";"""";",
"ODU_DSP_3;""HDLX2416SOCKETED"";""HDLX2416SOCKETED"";""HDLX2416(SOCKETED)"";""LED DISPLAY"";"""";"""";"""";"""";"""";"""";"""";"""";",
"ODU_DSP_4;""HDLX2416SOCKETED"";""HDLX2416SOCKETED"";""HDLX2416(SOCKETED)"";""LED DISPLAY"";"""";"""";"""";"""";"""";"""";"""";"""";",
"ODU_DSP_5;""HDLX2416SOCKETED"";""HDLX2416SOCKETED"";""HDLX2416(SOCKETED)"";""LED DISPLAY"";"""";"""";"""";"""";"""";"""";"""";"""";",
"ON/OFF;""GATERON-LED"";""GATERON-LED"";""GATERON-LED"";""Gateron keyswitch with LED"";"""";"""";"""";"""";"""";"""";"""";"""";",
"R1;""39K"";""R-EU_R1206"";""R1206"";""RESISTOR"," European symbol"";"""";"""";"""";"""";"""";""R"";"""";"""";"
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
